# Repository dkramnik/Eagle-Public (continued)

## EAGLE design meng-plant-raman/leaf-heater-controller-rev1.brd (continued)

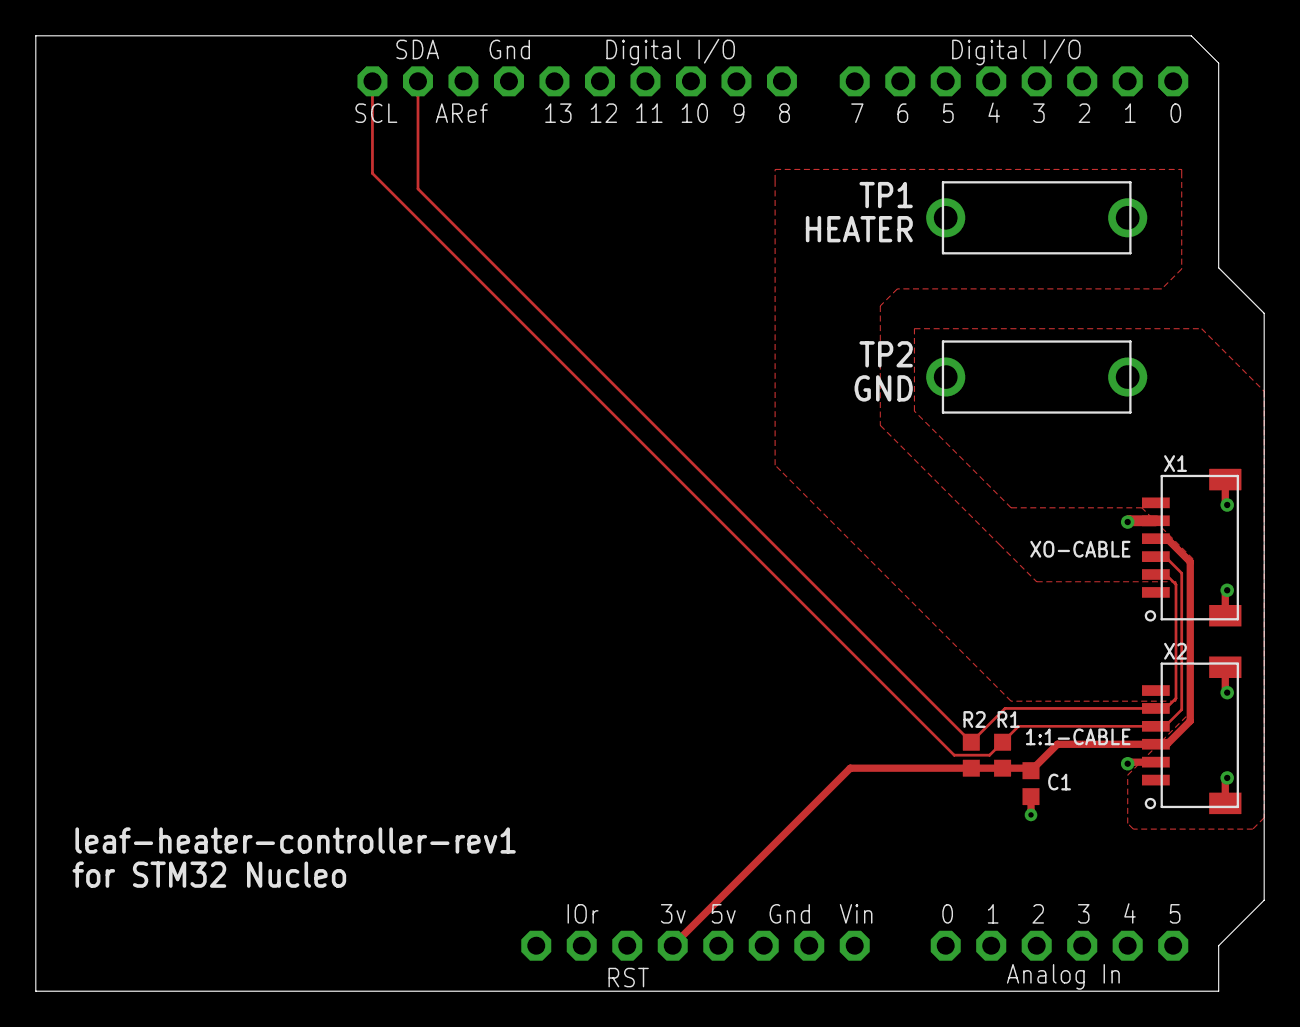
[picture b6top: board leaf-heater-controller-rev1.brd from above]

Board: 2 copper layers, 68.6 x 53.3 mm, 8 parts (0 on the bottom side), 6 nets.

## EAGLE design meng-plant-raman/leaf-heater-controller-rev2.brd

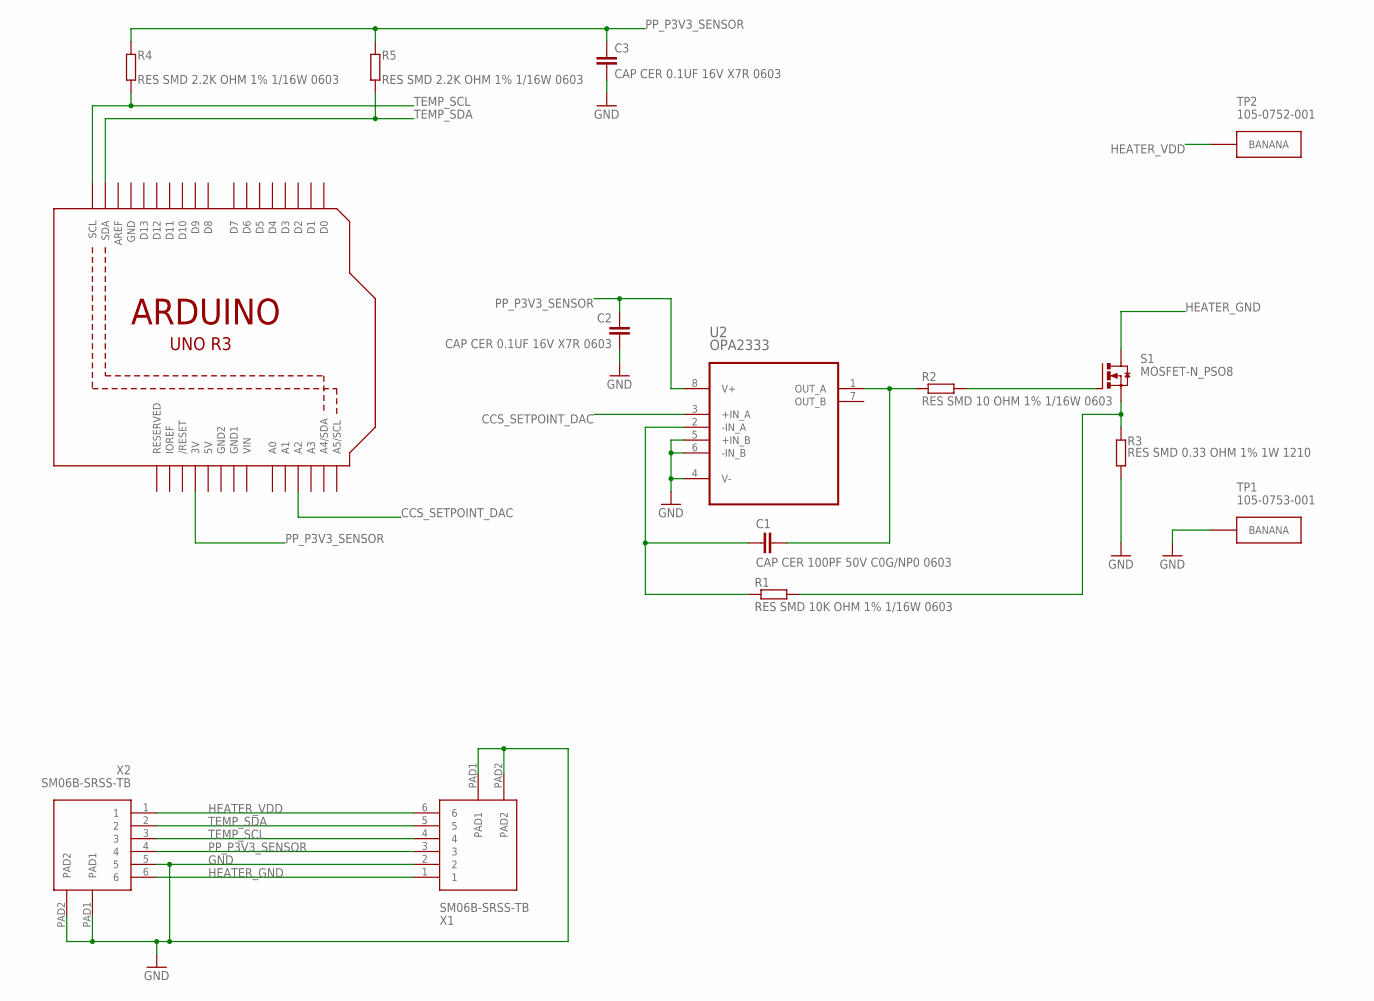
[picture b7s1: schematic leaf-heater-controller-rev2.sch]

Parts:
C1: CAP CER 100PF 50V C0G/NP0 0603; C0603
C2, C3: CAP CER 0.1UF 16V X7R 0603; C0603
R1: RES SMD 10K OHM 1% 1/16W 0603; R0603
R2: RES SMD 10 OHM 1% 1/16W 0603; R0603
R3: RES SMD 0.33 OHM 1% 1W 1210; R1210
R4, R5: RES SMD 2.2K OHM 1% 1/16W 0603; R0603
S1: MOSFET-N_PSO8; POWERSO8
TP1: 105-0753-001; CINCH-BANANA-105-075X-001
TP2: 105-0752-001; CINCH-BANANA-105-075X-001
U1: ARDUINOR3-DIMENSION; ARDUINOR3
U2: OPA2333; SOIC127P600X175-8N
X1, X2: SM06B-SRSS-TB; JST-SM06B-SRSS-TB

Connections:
5V: U1.5V
CCS_SETPOINT_DAC: U1.A2, U2.3 (+IN_A)
GND: C2.2, C3.2, R3.2, TP1.1, TP1.2, U1.GND, U2.4 (V-), U2.5 (+IN_B), U2.6 (-IN_B), X1.2, X1.PAD1, X1.PAD2, X2.5, X2.PAD1, X2.PAD2
GND1: U1.GND1
GND2: U1.GND2
HEATER_GND: S1.5 (D), S1.6 (D), S1.7 (D), S1.8 (D), S1.D, X1.1, X2.6
HEATER_VDD: TP2.1, TP2.2, X1.6, X2.1
unnamed: C1.2, R2.2, U2.1 (OUT_A)
unnamed: C1.1, R1.2, U2.2 (-IN_A)
unnamed: R2.1, S1.4 (G)
unnamed: R1.1, R3.1, S1.1 (S), S1.2 (S), S1.3 (S)
PP_P3V3_SENSOR: C2.1, C3.1, R4.2, R5.2, U1.3V, U2.8 (V+), X1.3, X2.4
TEMP_SCL: R4.1, U1.SCL, X1.4, X2.3
TEMP_SDA: R5.1, U1.SDA, X1.5, X2.2
VIN: U1.VIN

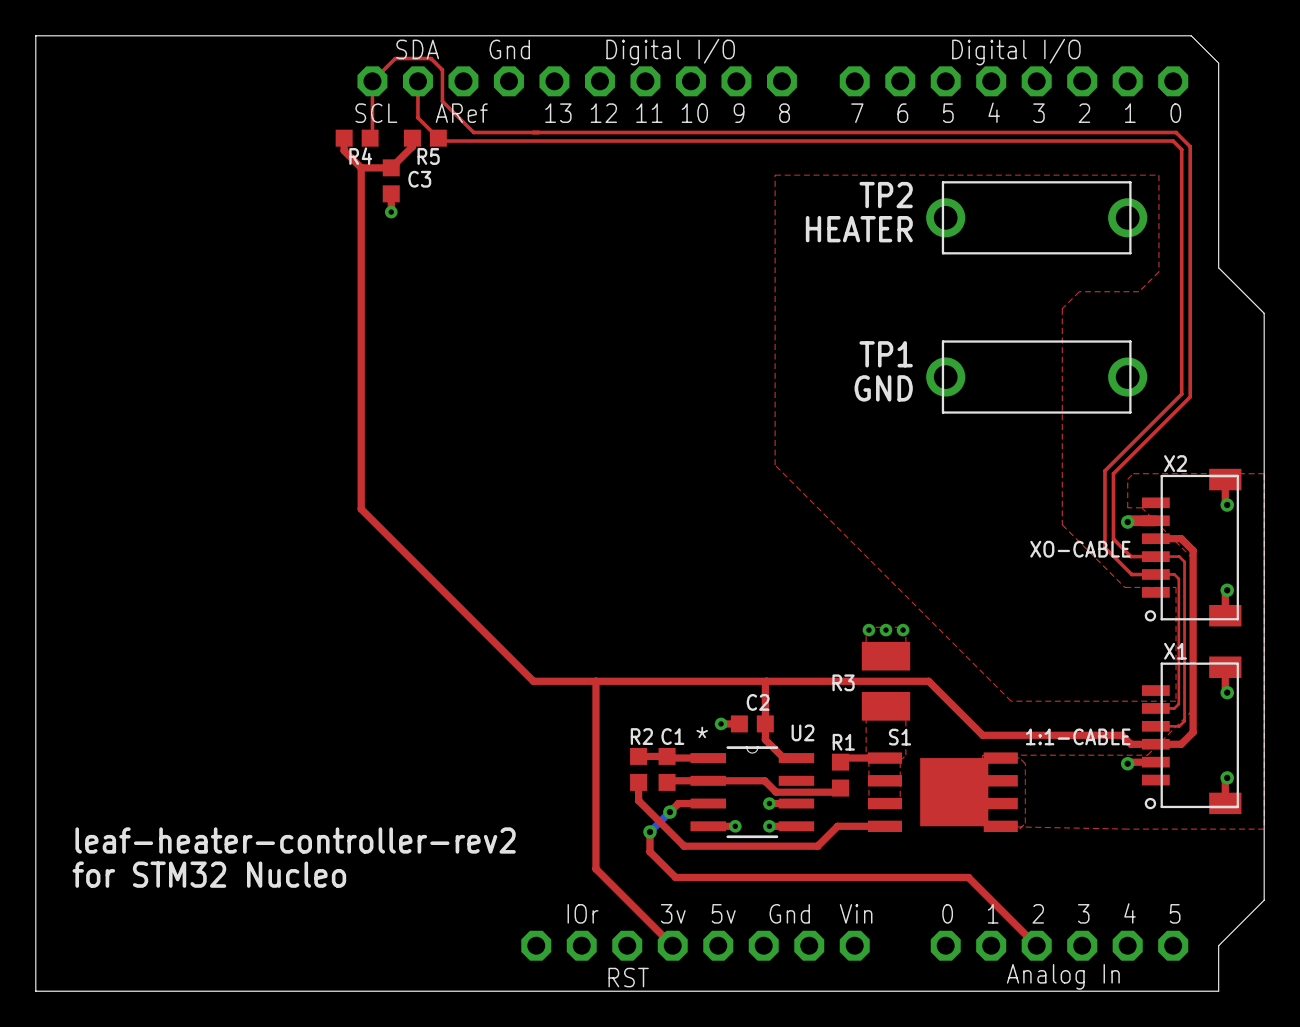
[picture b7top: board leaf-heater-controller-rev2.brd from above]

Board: 2 copper layers, 68.6 x 53.3 mm, 15 parts (0 on the bottom side), 11 nets.
